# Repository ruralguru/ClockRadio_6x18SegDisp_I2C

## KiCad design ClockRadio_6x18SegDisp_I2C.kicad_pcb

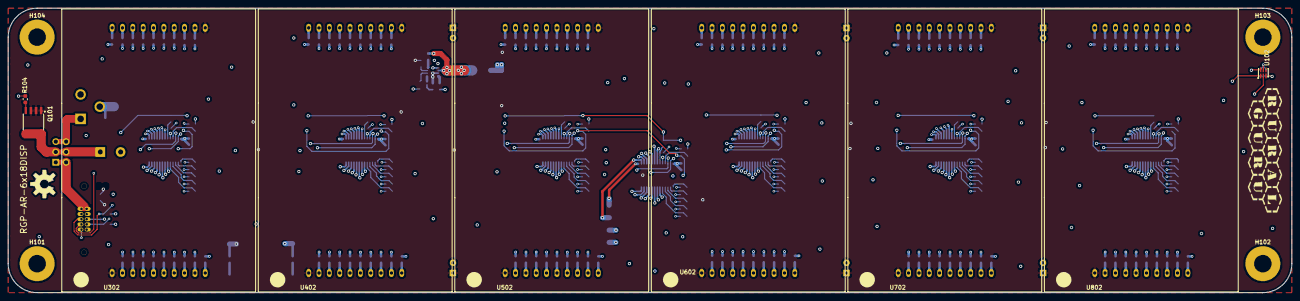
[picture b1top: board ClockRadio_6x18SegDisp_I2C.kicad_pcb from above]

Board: 4 copper layers, 315.2 x 69.9 mm, 297 parts (0 on the bottom side), 297 nets.

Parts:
C101: 680uF; CP_Radial_D12.5mm_P5.00mm
C102, C107: 22uF; C_0603_1608Metric
C103: 8.2nF; C_0201_0603Metric
C104, C105, C202, C302, C402, C502, C602, C702, C802: 0.1uF; C_0603_1608Metric
C106, C201, C301, C401, C501, C601, C701, C801: 1uF; C_0603_1608Metric
C303, C403, C503, C603, C703, C803: 100uF; CP_Radial_D6.3mm_P2.50mm
D101, D102: GRN; LED_0603_1608Metric_Castellated
G101, G102: RGP-AR-6x18DISP; OSHW-LOGO-L
G103, G104: LOGO; RuralguruProjects_HEX
G105, G106: RGP-AR-6x18DISP; OSHW-LOGO-L_COPPER
H101, H102, H103, H104: MountingHole_Pad; MountingHole_4.3mm_M4_Pad
J101: Display_tether; ESHF-105-01-L-D
J102: 5A; BarrelJack_CUI_PJ-102AH_Horizontal
J103: Voltage_Selection; PinHeader_2x03_P2.54mm_Vertical
L101: 3.3uH; INDC570X520X280
Q101: FDS6681Z; SO-8_5.3x6.2mm_P1.27mm
R101, R109, R207, R307, R407, R507, R607, R707, R807: 10k; R_0603_1608Metric
R102, R103, R104, R201, R202, R203, R204, R205, R206, R208, R209, R210, R211, R212, R213, R302, R303, R304, R305, R306, R308, R309, R310, R311, R312, R313, R402, R403, R404, R405, R406, R408, R409, R410, R411, R412, R413, R502, R503, R504, R505, R506, R508, R509, R510, R511, R512, R513, R602, R603, R604, R605, R606, R608, R609, R610, R611, R612, R613, R702, R703, R704, R705, R706, R708, R709, R710, R711, R712, R713, R802, R803, R804, R805, R806, R808, R809, R810, R811, R812, R813, R1001: 1k; R_0603_1608Metric
R105: 200Ω; R_0603_1608Metric
R106, R111, R112, R113, R114, R115, R116, R117, R118, R119, R120, R121, R122, R123, R124, R125, R126, R127, R128, R129, R130, R131: 0Ω; R_0603_1608Metric
R107: 100k; R_0603_1608Metric
R108: 33.2k; R_0603_1608Metric
R110: 120Ω; R_0603_1608Metric
R301, R401, R501, R601, R701, R801: 1K; R_0603_1608Metric
R314, R315, R316, R317, R318, R319, R320, R321, R323, R328, R414, R415, R416, R417, R418, R419, R420, R421, R423, R428, R514, R515, R516, R517, R518, R519, R520, R521, R523, R528, R614, R615, R616, R617, R618, R619, R620, R621, R623, R628, R714, R715, R716, R717, R718, R719, R720, R721, R723, R728, R814, R815, R816, R817, R818, R819, R820, R821, R823, R828: 15Ω; R_0603_1608Metric
R322, R331, R422, R431, R522, R531, R622, R631, R722, R731, R822, R831: 150Ω; R_0603_1608Metric
R324, R325, R326, R327, R329, R330, R424, R425, R426, R427, R429, R430, R524, R525, R526, R527, R529, R530, R624, R625, R626, R627, R629, R630, R724, R725, R726, R727, R729, R730, R824, R825, R826, R827, R829, R830: 27Ω; R_0603_1608Metric
TP101, TP102, TP103, TP104, TP105, TP106, TP107: TestPoint; TestPoint_Pad_D2.0mm
U101: TPS562219A; SOT-23-8
U102: TSL2591; DFN240X200X65-6
U201, U301, U401, U501, U601, U701, U801: PCA9685PW; TSSOP-28_4.4x9.7mm_P0.65mm
U302, U402, U502, U602, U702, U802: BL-S230B; BL-230X-13

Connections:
/CLK_EXT_0: R118.2, R125.2, U301.25
/CLK_EXT_1: R119.2, R126.2, U401.25
/CLK_EXT_2: R120.2, R127.2, U501.25
/CLK_EXT_3: R121.2, R128.2, U601.25
/CLK_EXT_4: R122.2, R129.2, U701.25
/CLK_EXT_5: R123.2, R130.2, U801.25
/CLK_EXT_GLOBAL: J101.10, R125.1, R126.1, R127.1, R128.1, R129.1, R130.1, R131.1
/DP0: R322.2, U201.9
/DP1: R331.2, U201.19
/DP2: R422.2, U201.10
/DP3: R431.2, U201.18
/DP4: R522.2, U201.11
/DP5: R531.2, U201.17
/DP6: R622.2, U201.6
/DP7: R631.2, U201.22
/DP8: R722.2, U201.7
/DP9: R731.2, U201.21
/DP10: R822.2, U201.8
/DP11: R831.2, U201.20
/Diplay_5/A0_SEL: R812.2, R813.1, U801.1
/Diplay_5/A1_SEL: R810.2, R811.1, U801.2
/Diplay_5/A2_SEL: R808.2, R809.1, U801.3
/Diplay_5/A3_SEL: R805.2, R806.1, U801.4
/Diplay_5/A4_SEL: R803.2, R804.1, U801.5
/Diplay_5/A5_SEL: R801.2, R802.1, U801.24
/Diplay_5/LED0: R823.2, U801.6
/Diplay_5/LED1: R814.2, U801.7
/Diplay_5/LED2: R824.2, U801.8
/Diplay_5/LED3: R815.2, U801.9
/Diplay_5/LED4: R817.2, U801.10
/Diplay_5/LED5: R826.2, U801.11
/Diplay_5/LED6: R816.2, U801.12
/Diplay_5/LED7: R825.2, U801.13
/Diplay_5/LED8: R828.2, U801.15
/Diplay_5/LED9: R819.2, U801.16
/Diplay_5/LED10: R827.2, U801.17
/Diplay_5/LED11: R818.2, U801.18
/Diplay_5/LED12: R820.2, U801.19
/Diplay_5/LED13: R829.2, U801.20
/Diplay_5/LED14: R821.2, U801.21
/Diplay_5/LED15: R830.2, U801.22
/Diplay_5/LED_A1: R827.1, U802.17
/Diplay_5/LED_A2: R829.1, U802.14
/Diplay_5/LED_B: R821.1, U802.13
/Diplay_5/LED_C: R823.1, U802.9
/Diplay_5/LED_D1: R826.1, U802.4
/Diplay_5/LED_D2: R824.1, U802.7
/Diplay_5/LED_DP0: R822.1, U802.10
/Diplay_5/LED_DP1: R831.1, U802.20
/Diplay_5/LED_E: R816.1, U802.3
/Diplay_5/LED_F: R828.1, U802.19
/Diplay_5/LED_G1: R825.1, U802.2
/Diplay_5/LED_G2: R830.1, U802.12
/Diplay_5/LED_H: R819.1, U802.18
/Diplay_5/LED_J: R818.1, U802.16
/Diplay_5/LED_K: R820.1, U802.15
/Diplay_5/LED_L: R814.1, U802.8
/Diplay_5/LED_M: R815.1, U802.6
/Diplay_5/LED_N: R817.1, U802.5
/Display_0/A0_SEL: R312.2, R313.1, U301.1
/Display_0/A1_SEL: R310.2, R311.1, U301.2
/Display_0/A2_SEL: R308.2, R309.1, U301.3
/Display_0/A3_SEL: R305.2, R306.1, U301.4
/Display_0/A4_SEL: R303.2, R304.1, U301.5
/Display_0/A5_SEL: R301.2, R302.1, U301.24
/Display_0/LED0: R323.2, U301.6
/Display_0/LED1: R314.2, U301.7
/Display_0/LED2: R324.2, U301.8
/Display_0/LED3: R315.2, U301.9
/Display_0/LED4: R317.2, U301.10
/Display_0/LED5: R326.2, U301.11
/Display_0/LED6: R316.2, U301.12
/Display_0/LED7: R325.2, U301.13
/Display_0/LED8: R328.2, U301.15
/Display_0/LED9: R319.2, U301.16
/Display_0/LED10: R327.2, U301.17
/Display_0/LED11: R318.2, U301.18
/Display_0/LED12: R320.2, U301.19
/Display_0/LED13: R329.2, U301.20
/Display_0/LED14: R321.2, U301.21
/Display_0/LED15: R330.2, U301.22
/Display_0/LED_A1: R327.1, U302.17
/Display_0/LED_A2: R329.1, U302.14
/Display_0/LED_B: R321.1, U302.13
/Display_0/LED_C: R323.1, U302.9
/Display_0/LED_D1: R326.1, U302.4
/Display_0/LED_D2: R324.1, U302.7
/Display_0/LED_DP0: R322.1, U302.10
/Display_0/LED_DP1: R331.1, U302.20
/Display_0/LED_E: R316.1, U302.3
/Display_0/LED_F: R328.1, U302.19
/Display_0/LED_G1: R325.1, U302.2
/Display_0/LED_G2: R330.1, U302.12
/Display_0/LED_H: R319.1, U302.18
/Display_0/LED_J: R318.1, U302.16
/Display_0/LED_K: R320.1, U302.15
/Display_0/LED_L: R314.1, U302.8
/Display_0/LED_M: R315.1, U302.6
/Display_0/LED_N: R317.1, U302.5
/Display_1/A0_SEL: R412.2, R413.1, U401.1
/Display_1/A1_SEL: R410.2, R411.1, U401.2
/Display_1/A2_SEL: R408.2, R409.1, U401.3
/Display_1/A3_SEL: R405.2, R406.1, U401.4
/Display_1/A4_SEL: R403.2, R404.1, U401.5
/Display_1/A5_SEL: R401.2, R402.1, U401.24
/Display_1/LED0: R423.2, U401.6
/Display_1/LED1: R414.2, U401.7
/Display_1/LED2: R424.2, U401.8
/Display_1/LED3: R415.2, U401.9
/Display_1/LED4: R417.2, U401.10
/Display_1/LED5: R426.2, U401.11
/Display_1/LED6: R416.2, U401.12
/Display_1/LED7: R425.2, U401.13
/Display_1/LED8: R428.2, U401.15
/Display_1/LED9: R419.2, U401.16
/Display_1/LED10: R427.2, U401.17
/Display_1/LED11: R418.2, U401.18
/Display_1/LED12: R420.2, U401.19
/Display_1/LED13: R429.2, U401.20
/Display_1/LED14: R421.2, U401.21
/Display_1/LED15: R430.2, U401.22
/Display_1/LED_A1: R427.1, U402.17
/Display_1/LED_A2: R429.1, U402.14
/Display_1/LED_B: R421.1, U402.13
/Display_1/LED_C: R423.1, U402.9
/Display_1/LED_D1: R426.1, U402.4
/Display_1/LED_D2: R424.1, U402.7
/Display_1/LED_DP0: R422.1, U402.10
/Display_1/LED_DP1: R431.1, U402.20
/Display_1/LED_E: R416.1, U402.3
/Display_1/LED_F: R428.1, U402.19
/Display_1/LED_G1: R425.1, U402.2
/Display_1/LED_G2: R430.1, U402.12
/Display_1/LED_H: R419.1, U402.18
/Display_1/LED_J: R418.1, U402.16
/Display_1/LED_K: R420.1, U402.15
/Display_1/LED_L: R414.1, U402.8
/Display_1/LED_M: R415.1, U402.6
/Display_1/LED_N: R417.1, U402.5
/Display_2/A0_SEL: R512.2, R513.1, U501.1
/Display_2/A1_SEL: R510.2, R511.1, U501.2
/Display_2/A2_SEL: R508.2, R509.1, U501.3
/Display_2/A3_SEL: R505.2, R506.1, U501.4
/Display_2/A4_SEL: R503.2, R504.1, U501.5
/Display_2/A5_SEL: R501.2, R502.1, U501.24
/Display_2/LED0: R523.2, U501.6
/Display_2/LED1: R514.2, U501.7
/Display_2/LED2: R524.2, U501.8
/Display_2/LED3: R515.2, U501.9
/Display_2/LED4: R517.2, U501.10
/Display_2/LED5: R526.2, U501.11
/Display_2/LED6: R516.2, U501.12
/Display_2/LED7: R525.2, U501.13
/Display_2/LED8: R528.2, U501.15
/Display_2/LED9: R519.2, U501.16
/Display_2/LED10: R527.2, U501.17
/Display_2/LED11: R518.2, U501.18
/Display_2/LED12: R520.2, U501.19
/Display_2/LED13: R529.2, U501.20
/Display_2/LED14: R521.2, U501.21
/Display_2/LED15: R530.2, U501.22
/Display_2/LED_A1: R527.1, U502.17
/Display_2/LED_A2: R529.1, U502.14
/Display_2/LED_B: R521.1, U502.13
/Display_2/LED_C: R523.1, U502.9
/Display_2/LED_D1: R526.1, U502.4
/Display_2/LED_D2: R524.1, U502.7
/Display_2/LED_DP0: R522.1, U502.10
/Display_2/LED_DP1: R531.1, U502.20
/Display_2/LED_E: R516.1, U502.3
/Display_2/LED_F: R528.1, U502.19
/Display_2/LED_G1: R525.1, U502.2
/Display_2/LED_G2: R530.1, U502.12
/Display_2/LED_H: R519.1, U502.18
/Display_2/LED_J: R518.1, U502.16
/Display_2/LED_K: R520.1, U502.15
/Display_2/LED_L: R514.1, U502.8
/Display_2/LED_M: R515.1, U502.6
/Display_2/LED_N: R517.1, U502.5
/Display_3/A0_SEL: R612.2, R613.1, U601.1
/Display_3/A1_SEL: R610.2, R611.1, U601.2
/Display_3/A2_SEL: R608.2, R609.1, U601.3
/Display_3/A3_SEL: R605.2, R606.1, U601.4
/Display_3/A4_SEL: R603.2, R604.1, U601.5
/Display_3/A5_SEL: R601.2, R602.1, U601.24
/Display_3/LED0: R623.2, U601.6
/Display_3/LED1: R614.2, U601.7
/Display_3/LED2: R624.2, U601.8
/Display_3/LED3: R615.2, U601.9
/Display_3/LED4: R617.2, U601.10
/Display_3/LED5: R626.2, U601.11
/Display_3/LED6: R616.2, U601.12
/Display_3/LED7: R625.2, U601.13
/Display_3/LED8: R628.2, U601.15
/Display_3/LED9: R619.2, U601.16
/Display_3/LED10: R627.2, U601.17
/Display_3/LED11: R618.2, U601.18
/Display_3/LED12: R620.2, U601.19
/Display_3/LED13: R629.2, U601.20
/Display_3/LED14: R621.2, U601.21
/Display_3/LED15: R630.2, U601.22
/Display_3/LED_A1: R627.1, U602.17
/Display_3/LED_A2: R629.1, U602.14
/Display_3/LED_B: R621.1, U602.13
/Display_3/LED_C: R623.1, U602.9
/Display_3/LED_D1: R626.1, U602.4
/Display_3/LED_D2: R624.1, U602.7
/Display_3/LED_DP0: R622.1, U602.10
/Display_3/LED_DP1: R631.1, U602.20
/Display_3/LED_E: R616.1, U602.3
/Display_3/LED_F: R628.1, U602.19
/Display_3/LED_G1: R625.1, U602.2
/Display_3/LED_G2: R630.1, U602.12
/Display_3/LED_H: R619.1, U602.18
/Display_3/LED_J: R618.1, U602.16
/Display_3/LED_K: R620.1, U602.15
/Display_3/LED_L: R614.1, U602.8
/Display_3/LED_M: R615.1, U602.6
/Display_3/LED_N: R617.1, U602.5
/Display_4/A0_SEL: R712.2, R713.1, U701.1
/Display_4/A1_SEL: R710.2, R711.1, U701.2
/Display_4/A2_SEL: R708.2, R709.1, U701.3
/Display_4/A3_SEL: R705.2, R706.1, U701.4
/Display_4/A4_SEL: R703.2, R704.1, U701.5
/Display_4/A5_SEL: R701.2, R702.1, U701.24
/Display_4/LED0: R723.2, U701.6
/Display_4/LED1: R714.2, U701.7
/Display_4/LED2: R724.2, U701.8
/Display_4/LED3: R715.2, U701.9
/Display_4/LED4: R717.2, U701.10
/Display_4/LED5: R726.2, U701.11
/Display_4/LED6: R716.2, U701.12
/Display_4/LED7: R725.2, U701.13
/Display_4/LED8: R728.2, U701.15
/Display_4/LED9: R719.2, U701.16
/Display_4/LED10: R727.2, U701.17
/Display_4/LED11: R718.2, U701.18
/Display_4/LED12: R720.2, U701.19
/Display_4/LED13: R729.2, U701.20
/Display_4/LED14: R721.2, U701.21
/Display_4/LED15: R730.2, U701.22
/Display_4/LED_A1: R727.1, U702.17
/Display_4/LED_A2: R729.1, U702.14
/Display_4/LED_B: R721.1, U702.13
/Display_4/LED_C: R723.1, U702.9
/Display_4/LED_D1: R726.1, U702.4
/Display_4/LED_D2: R724.1, U702.7
/Display_4/LED_DP0: R722.1, U702.10
/Display_4/LED_DP1: R731.1, U702.20
/Display_4/LED_E: R716.1, U702.3
/Display_4/LED_F: R728.1, U702.19
/Display_4/LED_G1: R725.1, U702.2
/Display_4/LED_G2: R730.1, U702.12
/Display_4/LED_H: R719.1, U702.18
/Display_4/LED_J: R718.1, U702.16
/Display_4/LED_K: R720.1, U702.15
/Display_4/LED_L: R714.1, U702.8
/Display_4/LED_M: R715.1, U702.6
/Display_4/LED_N: R717.1, U702.5
/EXT_CLK_DP: R124.2, R131.2, U201.25
/I2C_INT: J101.5, R1001.2, U102.2
/I2C_OE: J101.8, R111.2, R112.2, R113.2, R114.2, R115.2, R116.2, R117.2
/I2C_SCL: J101.7, R102.2, U102.1, U201.26, U301.26, U401.26, U501.26, U601.26, U701.26, U801.26
/I2C_SDA: J101.6, R103.2, U102.6, U201.27, U301.27, U401.27, U501.27, U601.27, U701.27, U801.27
/JACK_PRES: J102.3, R101.1, TP101.1
/LED_SPARE_1: TP104.1, U201.15
/LED_SPARE_2: TP105.1, U201.16
/LED_SPARE_3: TP106.1, U201.13
/LED_SPARE_4: TP107.1, U201.12
/OE_0: R111.1, R307.2, U301.23
/OE_1: R112.1, R407.2, U401.23
/OE_2: R113.1, R507.2, U501.23
/OE_3: R114.1, R607.2, U601.23
/OE_4: R115.1, R707.2, U701.23
/OE_5: R116.1, R807.2, U801.23
/OE_DP: R117.1, R207.2, U201.23
/V3P3_EN: R106.1, U101.7
/V3P3_LED: D102.1, R110.1
/V3P3_PG: R107.2, U101.4
/V3P3_SS: C103.1, U101.5
/V3P3_SW: C104.1, L101.1, U101.2
/V3P3_VBST: C104.2, U101.8
/V3P3_VFB: R108.2, R109.1, U101.6
/V6P0_JACK: J102.1, J103.5, J103.6
/V6P0_LED: D101.1, R105.1
/V6P0_RAW: C101.1, J103.3, J103.4, Q101.5, Q101.6, Q101.7, Q101.8
GND: C101.2, C102.2, C103.2, C105.2, C106.2, C107.2, C201.2, C202.2, C301.2, C302.2, C303.2, C401.2, C402.2, C403.2, C501.2, C502.2, C503.2, C601.2, C602.2, C603.2, C701.2, C702.2, C703.2, C801.2, C802.2, C803.2, H101.1, H102.1, H103.1, H104.1, J101.3, J101.4, J101.9, J102.2, R101.2, R104.1, R105.2, R109.2, R110.2, R118.1, R119.1, R120.1, R121.1, R122.1, R123.1, R124.1, R202.2, R204.2, R206.2, R209.2, R211.2, R213.2, R302.2, R304.2, R306.2, R309.2, R311.2, R313.2, R402.2, R404.2, R406.2, R409.2, R411.2, R413.2, R502.2, R504.2, R506.2, R509.2, R511.2, R513.2, R602.2, R604.2, R606.2, R609.2, R611.2, R613.2, R702.2, R704.2, R706.2, R709.2, R711.2, R713.2, R802.2, R804.2, R806.2, R809.2, R811.2, R813.2, U101.1, U102.3, U201.14, U301.14, U401.14, U501.14, U601.14, U701.14, U801.14
unnamed: Q101.4, R104.2
unnamed: R201.2, R202.1, U201.24
unnamed: R203.2, R204.1, U201.5
unnamed: R205.2, R206.1, U201.4
unnamed: R208.2, R209.1, U201.3
unnamed: R210.2, R211.1, U201.2
unnamed: R212.2, R213.1, U201.1
V3P3: C105.1, C106.1, C107.1, C201.1, C202.1, C301.1, C302.1, C401.1, C402.1, C501.1, C502.1, C601.1, C602.1, C701.1, C702.1, C801.1, C802.1, D102.2, L101.2, R102.1, R103.1, R107.1, R108.1, R201.1, R203.1, R205.1, R207.1, R208.1, R210.1, R212.1, R301.1, R303.1, R305.1, R307.1, R308.1, R310.1, R312.1, R401.1, R403.1, R405.1, R407.1, R408.1, R410.1, R412.1, R501.1, R503.1, R505.1, R507.1, R508.1, R510.1, R512.1, R601.1, R603.1, R605.1, R607.1, R608.1, R610.1, R612.1, R701.1, R703.1, R705.1, R707.1, R708.1, R710.1, R712.1, R801.1, R803.1, R805.1, R807.1, R808.1, R810.1, R812.1, R1001.1, TP103.1, U102.5, U201.28, U301.28, U401.28, U501.28, U601.28, U701.28, U801.28
V6P0: C102.1, C303.1, C403.1, C503.1, C603.1, C703.1, C803.1, D101.2, Q101.1, Q101.2, Q101.3, R106.2, TP102.1, U101.3, U302.1, U302.11, U402.1, U402.11, U502.1, U502.11, U602.1, U602.11, U702.1, U702.11, U802.1, U802.11
V6P0_SYSTEM: J101.1, J101.2, J103.1, J103.2

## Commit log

2019-05-24 Package For Fab
    Rev 1.0.0
2019-05-25 Commiting to the online
2019-05-25 Updated Documentation Rev 1.0.0
    - Finished Critical Fabrication Dimensions.
    - Added Comments about Board.
2019-05-25 Cleanup
    File Organization
2019-05-25 Another Document Addition
    Added Block Diagram
2019-05-25 Another Document Addition
    Added BOM to BOM's name
2019-07-02 Post assembly updates. Added pullup, R1001, for LUX sensor INT line. Changed R104 to 1k resolving issue.
2019-07-14 Schematic and Populated Components added.
